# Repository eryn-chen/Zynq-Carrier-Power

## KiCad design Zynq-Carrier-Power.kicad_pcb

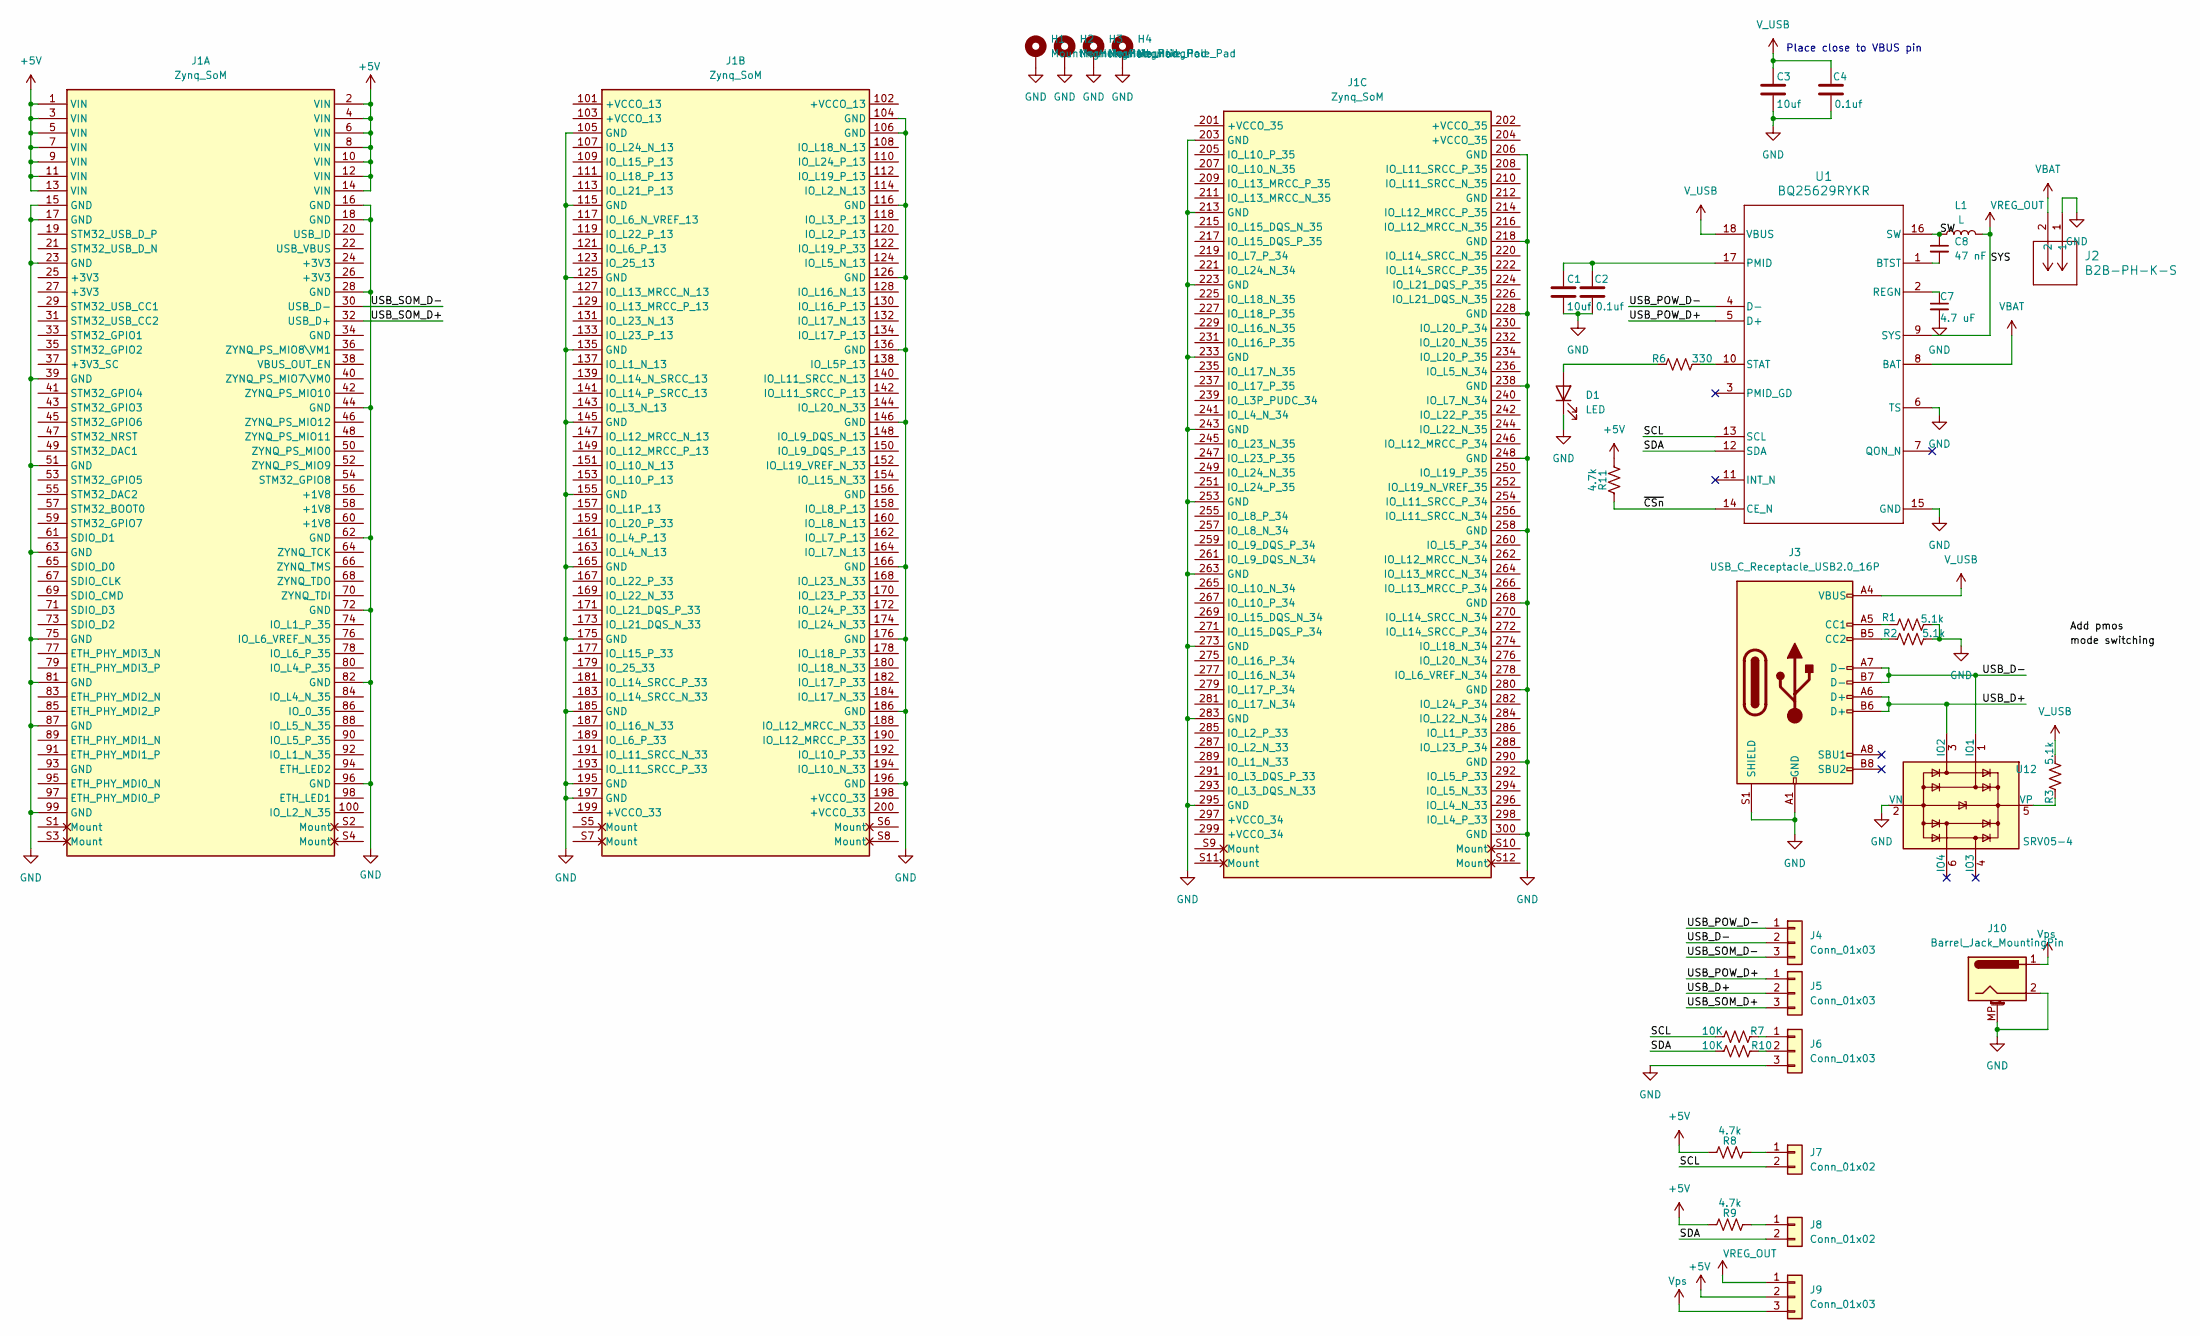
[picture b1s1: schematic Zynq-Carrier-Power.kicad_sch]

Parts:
C1, C3: 10uf; C_0603_1608Metric
C2, C4: 0.1uf; C_0603_1608Metric
C7: 4.7 uF; C_0603_1608Metric
C8: 47 nF; C_0603_1608Metric
D1: LED; LED_0805_2012Metric
H1, H2, H3, H4: MountingHole_Pad; MountingHole_2.5mm_Pad_TopBottom
J1: Zynq_SoM
J2: B2B-PH-K-S; CONN2_B2B-PH-K-S_JST
J3: USB_C_Receptacle_USB2.0_16P; USB_C_Receptacle_G-Switch_GT-USB-7010ASV
J4, J5, J6, J9: Conn_01x03; PinHeader_1x03_P2.54mm_Vertical
J7, J8: Conn_01x02; PinHeader_1x02_P2.54mm_Vertical
J10: Barrel_Jack_MountingPin; BarrelJack_Horizontal
L1: L; L_1008_2520Metric_Pad1.43x2.20mm_HandSolder
R1, R2, R3: 5.1k; R_0603_1608Metric
R6: 330; R_0603_1608Metric
R7, R10: 10K; R_0603_1608Metric
R8, R9, R11: 4.7k; R_0603_1608Metric
U1: BQ25629RYKR; RYK0018A-MFG
U12: SRV05-4; SOT-23-6; LCSC C85364

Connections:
+5V: J1.1 (VIN), J1.2 (VIN), J1.3 (VIN), J1.4 (VIN), J1.5 (VIN), J1.6 (VIN), J1.7 (VIN), J1.8 (VIN), J1.9 (VIN), J1.10 (VIN), J1.11 (VIN), J1.12 (VIN), J1.13 (VIN), J1.14 (VIN), J9.2, R8.1, R9.1, R11.2
/SCL: J7.2, R7.1, U1.13 (SCL)
/SDA: J8.2, R10.1, U1.12 (SDA)
/SW: C8.1, L1.1, U1.16 (SW)
/USB_D+: J3.A6 (D+), J3.B6 (D+), J5.2, U12.3 (IO2)
/USB_D-: J3.A7 (D-), J3.B7 (D-), J4.2, U12.1 (IO1)
/USB_POW_D+: J5.1, U1.5 (D+)
/USB_POW_D-: J4.1, U1.4 (D-)
/USB_SOM_D+: J1.32 (USB_D+), J5.3
/USB_SOM_D-: J1.30 (USB_D-), J4.3
/~CSn: R11.1, U1.14 (CE_N)
GND: C1.2, C2.2, C3.2, C4.2, C7.2, D1.1 (K), H1.1, H2.1, H3.1, H4.1, J1.15 (GND), J1.16 (GND), J1.17 (GND), J1.18 (GND), J1.23 (GND), J1.28 (GND), J1.39 (GND), J1.44 (GND), J1.51 (GND), J1.62 (GND), J1.63 (GND), J1.72 (GND), J1.75 (GND), J1.81 (GND), J1.82 (GND), J1.87 (GND), J1.96 (GND), J1.99 (GND), J1.104 (GND), J1.105 (GND), J1.106 (GND), J1.115 (GND), J1.116 (GND), J1.125 (GND), J1.126 (GND), J1.135 (GND), J1.136 (GND), J1.145 (GND), J1.146 (GND), J1.155 (GND), J1.165 (GND), J1.166 (GND), J1.175 (GND), J1.176 (GND), J1.185 (GND), J1.186 (GND), J1.195 (GND), J1.196 (GND), J1.197 (GND), J1.203 (GND), J1.206 (GND), J1.213 (GND), J1.218 (GND), J1.223 (GND), J1.228 (GND), J1.233 (GND), J1.238 (GND), J1.243 (GND), J1.248 (GND), J1.253 (GND), J1.258 (GND), J1.263 (GND), J1.268 (GND), J1.273 (GND), J1.280 (GND), J1.283 (GND), J1.290 (GND), J1.295 (GND), J1.300 (GND), J2.1, J3.A1 (GND), J3.A12 (GND), J3.B1 (GND), J3.B12 (GND), J3.S1 (SHIELD), J6.3, J10.2, J10.MP (MountPin), R1.1, R2.1, U1.6 (TS), U1.15 (GND), U12.2 (VN)
unnamed: D1.2 (A), R6.2
unnamed: J3.A5 (CC1), R1.2
unnamed: J3.B5 (CC2), R2.2
unnamed: J6.1, R7.2
unnamed: J6.2, R10.2
unnamed: J7.1, R8.2
unnamed: J8.1, R9.2
unnamed: C8.2, U1.1 (BTST)
unnamed: C1.1, C2.1, U1.17 (PMID)
unnamed: C7.1, U1.2 (REGN)
unnamed: R6.1, U1.10 (STAT)
unnamed: R3.2, U12.5 (VP)
VBAT: J2.2, U1.8 (BAT)
VREG_OUT: J9.1, L1.2, U1.9 (SYS)
V_USB: C3.1, C4.1, J3.A4 (VBUS), J3.A9 (VBUS), J3.B4 (VBUS), J3.B9 (VBUS), R3.1, U1.18 (VBUS)
Vps: J9.3, J10.1

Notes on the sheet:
Place close to VBUS pin

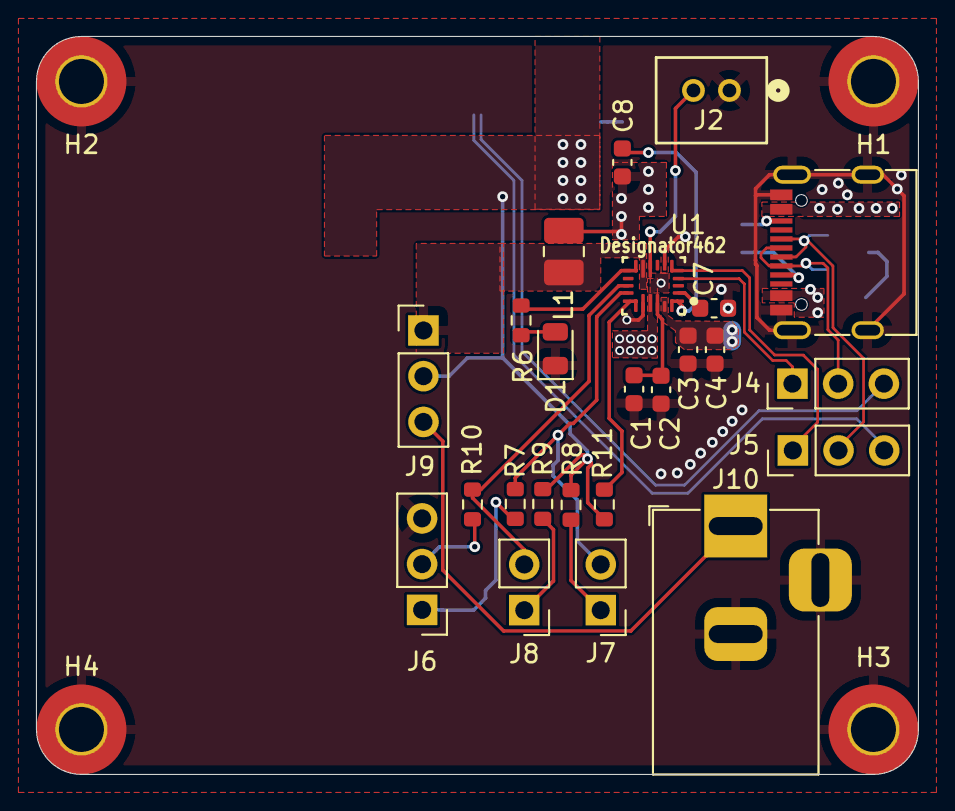
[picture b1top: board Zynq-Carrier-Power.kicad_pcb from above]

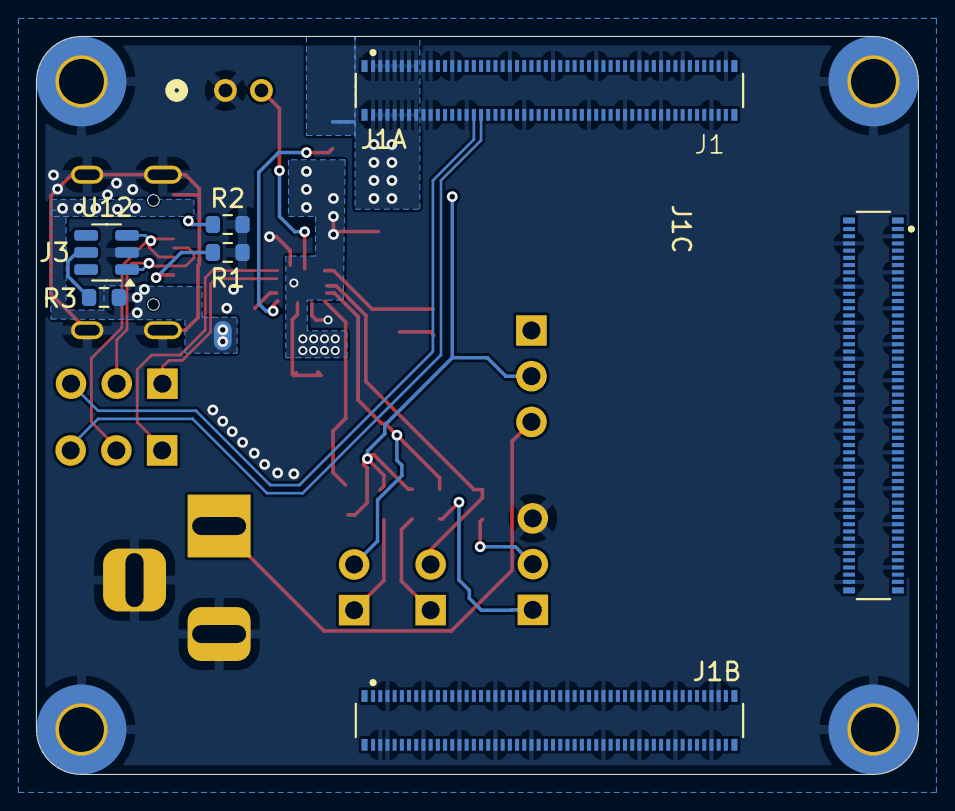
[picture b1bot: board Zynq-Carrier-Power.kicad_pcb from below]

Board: 2 copper layers, 49.0 x 41.0 mm, 33 parts (5 on the bottom side), 28 nets.

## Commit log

2025-07-26 Testing collab functionality
2025-07-26 Import BQ25629RYKR
2025-07-26 Copper Fill demo
2025-07-26 3D Model BQ25629RYKR
2025-07-28 Import 1uH Inductor
2025-07-28 Added USB-C 3D Model
2025-07-28 Import JST_Pins and Inductor
2025-07-28 USB-C Schematic
2025-08-07 Updated Schematic Switching Regulator Output
2025-08-27 Began work on PCB design for Zynq Carrier
2025-08-27 Updated PCB components
2025-09-03 Some errors corrected
2025-09-03 resolved drc errors
2025-09-03 Capacitor Relocation
2025-09-10 routed D+D-
2025-09-14 Moved barrel jack & routed a differential pair
2025-09-17 More Connections & DRC
2025-09-24 Finished Connections
2025-10-07 Modified Vias and Reorganized
2025-10-15 Fixed More PCB Errors
2025-10-31 Fixed most DRC errors
2025-10-31 Modified VREG_OUT & Silkscreen
2025-11-06 edited DRC constraints
2025-11-09 Modified PCB & Schematic for new constraints
    Modifications are not done yet. Some errors are still present
2025-11-11 Updated V_USB Connections
2025-11-11 Fixed Final Errors
    Only errors left are small thermal relief issues that are a part of the zynq carrier footprint.
2026-02-06 Organized the PCB Layout
